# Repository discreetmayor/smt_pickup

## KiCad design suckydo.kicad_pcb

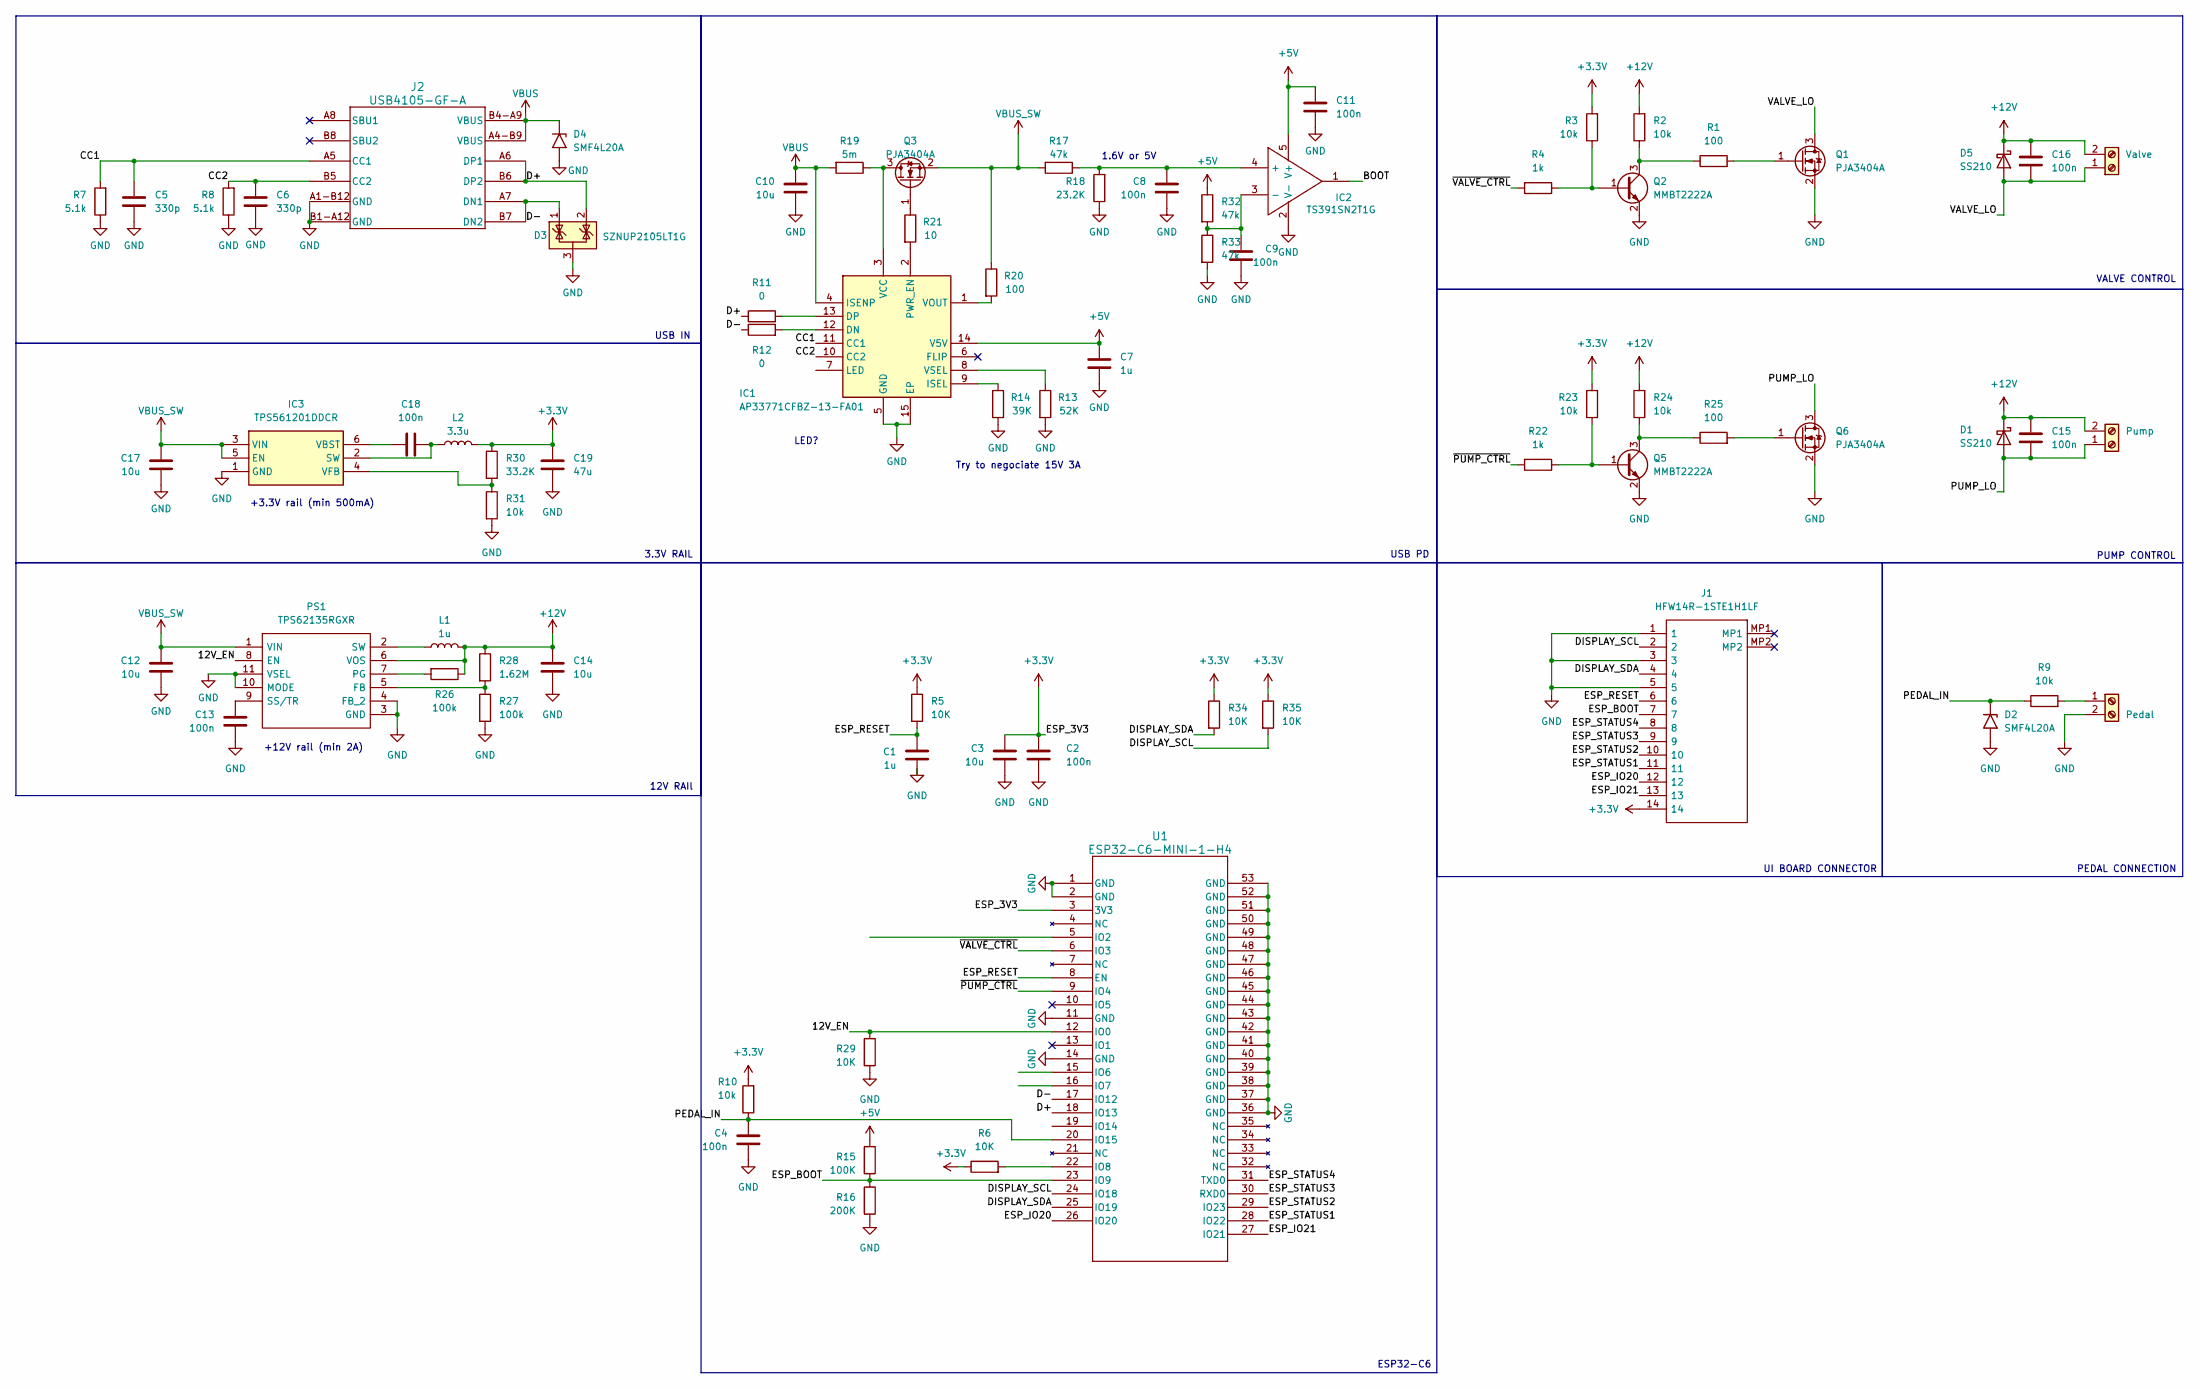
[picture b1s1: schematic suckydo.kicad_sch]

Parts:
C1, C7: 1u; C_0805_2012Metric
C2, C4: 100n; C_0805_2012Metric; Part KGM05AR71C104KH
C3: 10u; C_0805_2012Metric; Part KGM05AR71C104KH
C5, C6: 330p; C_0805_2012Metric; Part KGM05AR71C104KH
C8, C9, C11, C13, C15, C16, C18: 100n; C_0805_2012Metric
C10, C12, C14, C17: 10u; R_1210_3225Metric; Part KGM05AR71C104KH
C19: 47u; C_1206_3216Metric; Part KGM05AR71C104KH
D1, D5: SS210; D_SMA
D2, D4: SMF4L20A; D_SOD-123F
D3: SZNUP2105LT1G; SOT-23; Part SZNUP2105LT1G
IC1: AP33771CFBZ-13-FA01; AP33771CFBZ13FA01; Mouser Part Number 621-P33771CFBZ13FA01
IC2: TS391SN2T1G; SOT95P275X110-5N; Mouser Part Number 863-TS391SN2T1G
IC3: TPS561201DDCR; SOT95P280X110-6N; Mouser Part Number 595-TPS561201DDCR
J1: HFW14R-1STE1H1LF; HFW14R1STE1H1LF; Manufacturer_Part_Number HFW14R-1STE1H1LF
J2: USB4105-GF-A; USB4105_GCT
L1: 1u; XAL40XX
L2: 3.3u; L_1008_2520Metric
PS1: TPS62135RGXR; TPS621361RGXT; Mouser Part Number 595-TPS62135RGXR
Pedal1: Pedal; TerminalBlock_TE_282834-2_1x02_P2.54mm_Horizontal
Pump1: Pump; TerminalBlock_TE_282834-2_1x02_P2.54mm_Horizontal
Q1, Q3, Q6: PJA3404A; SOT-23
Q2, Q5: MMBT2222A; SOT-23
R1, R25: 100; R_0805_2012Metric
R2, R3, R9, R10, R23, R24, R31: 10k; R_0805_2012Metric
R4, R22: 1k; R_0805_2012Metric
R5, R6, R29, R34, R35: 10K; R_0805_2012Metric; Part RT0402FRE0722KL
R7, R8: 5.1k; R_0805_2012Metric
R11, R12: 0; R_0805_2012Metric; Part RT0402FRE0722KL
R13: 52K; R_0805_2012Metric; Part RT0402FRE0722KL
R14: 39K; R_0805_2012Metric; Part RT0402FRE0722KL
R15: 100K; R_0805_2012Metric; Part RT0402FRE0722KL
R16: 200K; R_0805_2012Metric; Part RT0402FRE0722KL
R17, R32, R33: 47k; R_0805_2012Metric
R18: 23.2K; R_0805_2012Metric
R19: 5m; R_0805_2012Metric
R20: 100; R_0805_2012Metric; Part RT0402FRE0722KL
R21: 10; R_0805_2012Metric; Part RT0402FRE0722KL
R26, R27: 100k; R_0805_2012Metric
R28: 1.62M; R_0805_2012Metric
R30: 33.2K; R_0805_2012Metric
U1: ESP32-C6-MINI-1-H4; ESP32-C6_EXP
Valve1: Valve; TerminalBlock_TE_282834-2_1x02_P2.54mm_Horizontal

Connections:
+3.3V: C2.1, C3.1, C19.1, J1.14, L2.2, R3.2, R5.1, R6.1, R10.2, R23.2, R30.1, R34.1, R35.1, U1.3 (3V3)
+5V: C7.1, C11.1, IC1.14 (V5V), IC2.5 (V+), R15.1, R32.1
+12V: C14.1, C15.1, C16.1, D1.1 (K), D5.1 (K), L1.2, PS1.6 (VOS), Pump1.2, R2.2, R24.2, R26.1, R28.1, Valve1.2
/12V_EN: PS1.8 (EN), R29.1, U1.12 (IO0)
/BOOT: IC2.1
/CC1: C5.1, IC1.11 (CC1), J2.A5 (CC1), R7.2
/CC2: C6.1, IC1.10 (CC2), J2.B5 (CC2), R8.2
/D+: D3.2 (K), J2.A6 (DP1), J2.B6 (DP2), R11.1, U1.18 (IO13)
/D-: D3.1 (K), J2.A7 (DN1), J2.B7 (DN2), R12.1, U1.17 (IO12)
/DISPLAY_SCL: J1.2, R35.2, U1.24 (IO18)
/DISPLAY_SDA: J1.4, R34.2, U1.25 (IO19)
/ESP_BOOT: J1.7, R15.2, R16.1, U1.23 (IO9)
/ESP_IO20: J1.12, U1.26 (IO20)
/ESP_IO21: J1.13, U1.27 (IO21)
/ESP_RESET: C1.1, J1.6, R5.2, U1.8 (EN)
/ESP_STATUS1: J1.11, U1.28 (IO22)
/ESP_STATUS2: J1.10, U1.29 (IO23)
/ESP_STATUS3: J1.9, U1.30 (RXD0)
/ESP_STATUS4: J1.8, U1.31 (TXD0)
/PEDAL_IN: C4.1, D2.1 (A1), R9.1, R10.1, U1.20 (IO15)
/PUMP_LO: C15.2, D1.2 (A), Pump1.1, Q6.3 (D)
/VALVE_LO: C16.2, D5.2 (A), Q1.3 (D), Valve1.1
/~PUMP_CTRL: R22.2, U1.9 (IO4)
/~VALVE_CTRL: R4.2, U1.6 (IO3)
GND: C1.2, C2.2, C3.2, C4.2, C5.2, C6.2, C7.2, C8.2, C9.2, C10.2, C11.2, C12.2, C13.2, C14.2, C17.2, C19.2, D2.2 (A2), D3.3 (A), D4.2 (A2), IC1.5 (GND), IC1.15 (EP), IC2.2 (V-), IC3.1 (GND), J1.1, J1.3, J1.5, J2.A1-B12 (GND), J2.B1-A12 (GND), PS1.3 (GND), PS1.4 (FB_2), PS1.10 (MODE), PS1.11 (VSEL), Pedal1.2, Q1.2 (S), Q2.2 (E), Q5.2 (E), Q6.2 (S), R7.1, R8.1, R13.2, R14.2, R16.2, R18.1, R27.2, R29.2, R31.2, R33.2, U1.1 (GND), U1.2 (GND), U1.11 (GND), U1.14 (GND), U1.36 (GND), U1.37 (GND), U1.38 (GND), U1.39 (GND), U1.40 (GND), U1.41 (GND), U1.42 (GND), U1.43 (GND), U1.44 (GND), U1.45 (GND), U1.46 (GND), U1.47 (GND), U1.48 (GND), U1.49 (GND), U1.50 (GND), U1.51 (GND), U1.52 (GND), U1.53 (GND)
unnamed: IC1.12 (DN), R12.2
unnamed: IC1.13 (DP), R11.2
unnamed: IC1.9 (ISEL), R14.1
unnamed: IC1.2 (PWR_EN), R21.2
unnamed: IC1.3 (VCC), Q3.3 (D), R19.1
unnamed: IC1.1 (VOUT), R20.2
unnamed: IC1.8 (VSEL), R13.1
unnamed: C8.1, IC2.4 (+), R17.1, R18.2
unnamed: C9.1, IC2.3 (-), R32.2, R33.1
unnamed: C18.2, IC3.2 (SW), L2.1
unnamed: C18.1, IC3.6 (VBST)
unnamed: IC3.4 (VFB), R30.2, R31.1
unnamed: PS1.5 (FB), R27.1, R28.2
unnamed: PS1.7 (PG), R26.2
unnamed: C13.1, PS1.9 (SS/TR)
unnamed: L1.1, PS1.2 (SW)
unnamed: Pedal1.1, R9.2
unnamed: Q1.1 (G), R1.2
unnamed: Q2.1 (B), R3.1, R4.1
unnamed: Q2.3 (C), R1.1, R2.1
unnamed: Q3.1 (G), R21.1
unnamed: Q5.1 (B), R22.1, R23.1
unnamed: Q5.3 (C), R24.1, R25.1
unnamed: Q6.1 (G), R25.2
unnamed: R6.2, U1.22 (IO8)
VBUS: C10.1, D4.1 (A1), IC1.4 (ISENP), J2.A4-B9 (VBUS), J2.B4-A9 (VBUS), R19.2
VBUS_SW: C12.1, C17.1, IC3.3 (VIN), IC3.5 (EN), PS1.1 (VIN), Q3.2 (S), R17.2, R20.1

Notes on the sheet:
LED?
PUMP CONTROL
UI BOARD CONNECTOR
12V RAIl
Try to negociate 15V 3A
3.3V RAIL
+12V rail (min 2A)
+3.3V rail (min 500mA)
USB PD
1.6V or 5V
ESP32-C6
USB IN
PEDAL CONNECTION
VALVE CONTROL

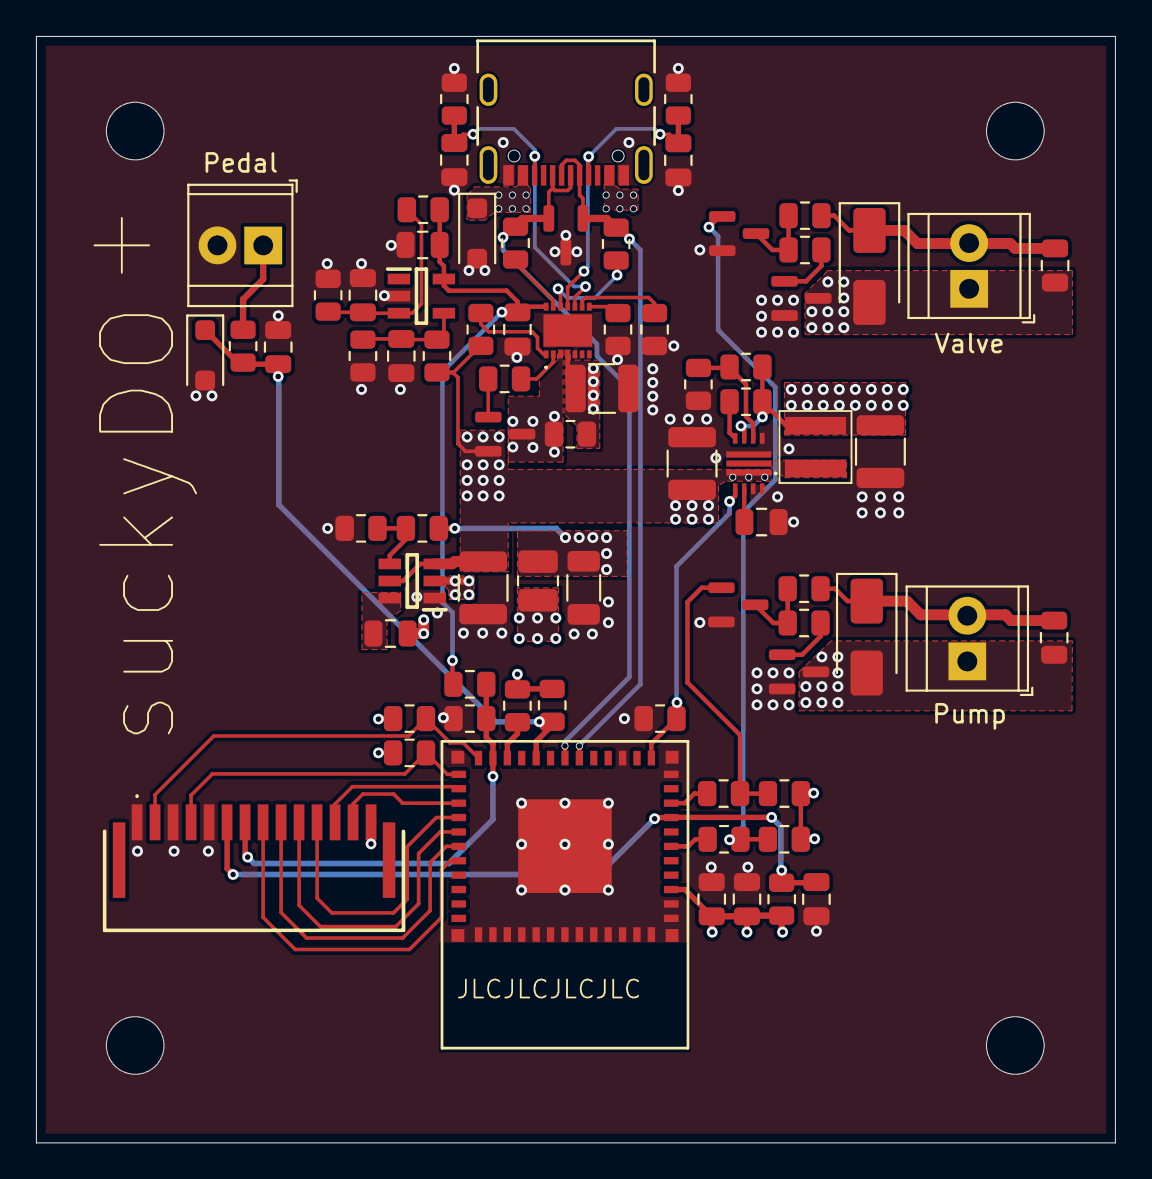
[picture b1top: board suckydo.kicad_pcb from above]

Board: 4 copper layers, 59.9 x 61.5 mm, 76 parts (0 on the bottom side), 51 nets.

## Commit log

2025-01-10 inial commit
2025-01-10 a bit more room
2025-01-10 ...and a small cleanup
2025-01-12 USB PD, MOSFET pump control, auto ESP boot mode
2025-01-12 note to check TVS on VBUS
2025-01-14 regulators
2025-01-15 tweaks
2025-01-15 double checked comparator
2025-01-15 ui board connector and cleanup
2025-01-15 status IOs
2025-01-15 footprints
2025-01-17 layout
2025-01-17 drc fixes
2025-01-17 drill size fixes
